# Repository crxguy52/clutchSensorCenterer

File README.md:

# clutchSensorCenterer

For centering the clutch sensor potentiometer in the ECU's expected range (10-90%)

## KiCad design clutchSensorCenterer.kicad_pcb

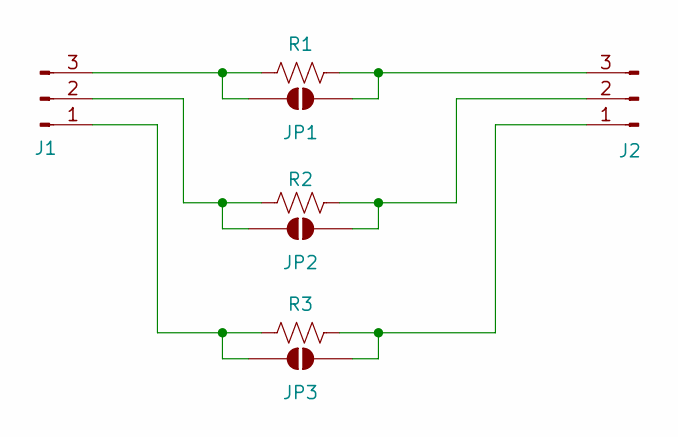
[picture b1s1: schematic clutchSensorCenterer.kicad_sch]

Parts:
J1, J2: Conn_01x03_Pin; PinHeader_1x03_P2.54mm_Vertical
JP1, JP2, JP3: SolderJumper_2_Open; SolderJumper-2_P1.3mm_Open_Pad1.0x1.5mm
R1, R2, R3: R_US; R_1206_3216Metric_Pad1.30x1.75mm_HandSolder

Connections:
unnamed: J1.1, JP3.1 (A), R3.1
unnamed: J1.2, JP2.1 (A), R2.1
unnamed: J1.3, JP1.1 (A), R1.1
unnamed: J2.1, JP3.2 (B), R3.2
unnamed: J2.2, JP2.2 (B), R2.2
unnamed: J2.3, JP1.2 (B), R1.2

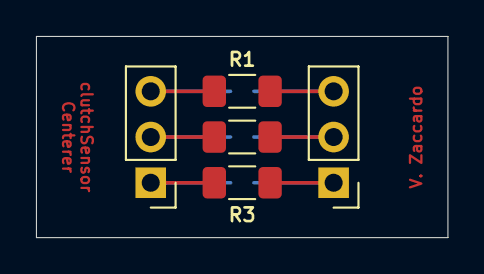
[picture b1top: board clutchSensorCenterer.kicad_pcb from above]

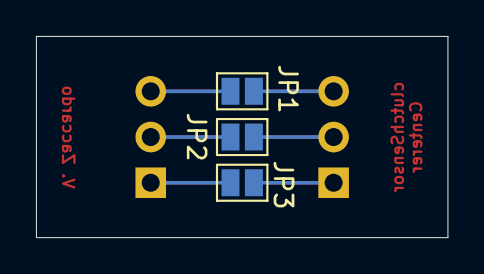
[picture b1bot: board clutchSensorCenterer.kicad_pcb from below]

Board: 2 copper layers, 22.9 x 11.2 mm, 8 parts (3 on the bottom side), 6 nets.
